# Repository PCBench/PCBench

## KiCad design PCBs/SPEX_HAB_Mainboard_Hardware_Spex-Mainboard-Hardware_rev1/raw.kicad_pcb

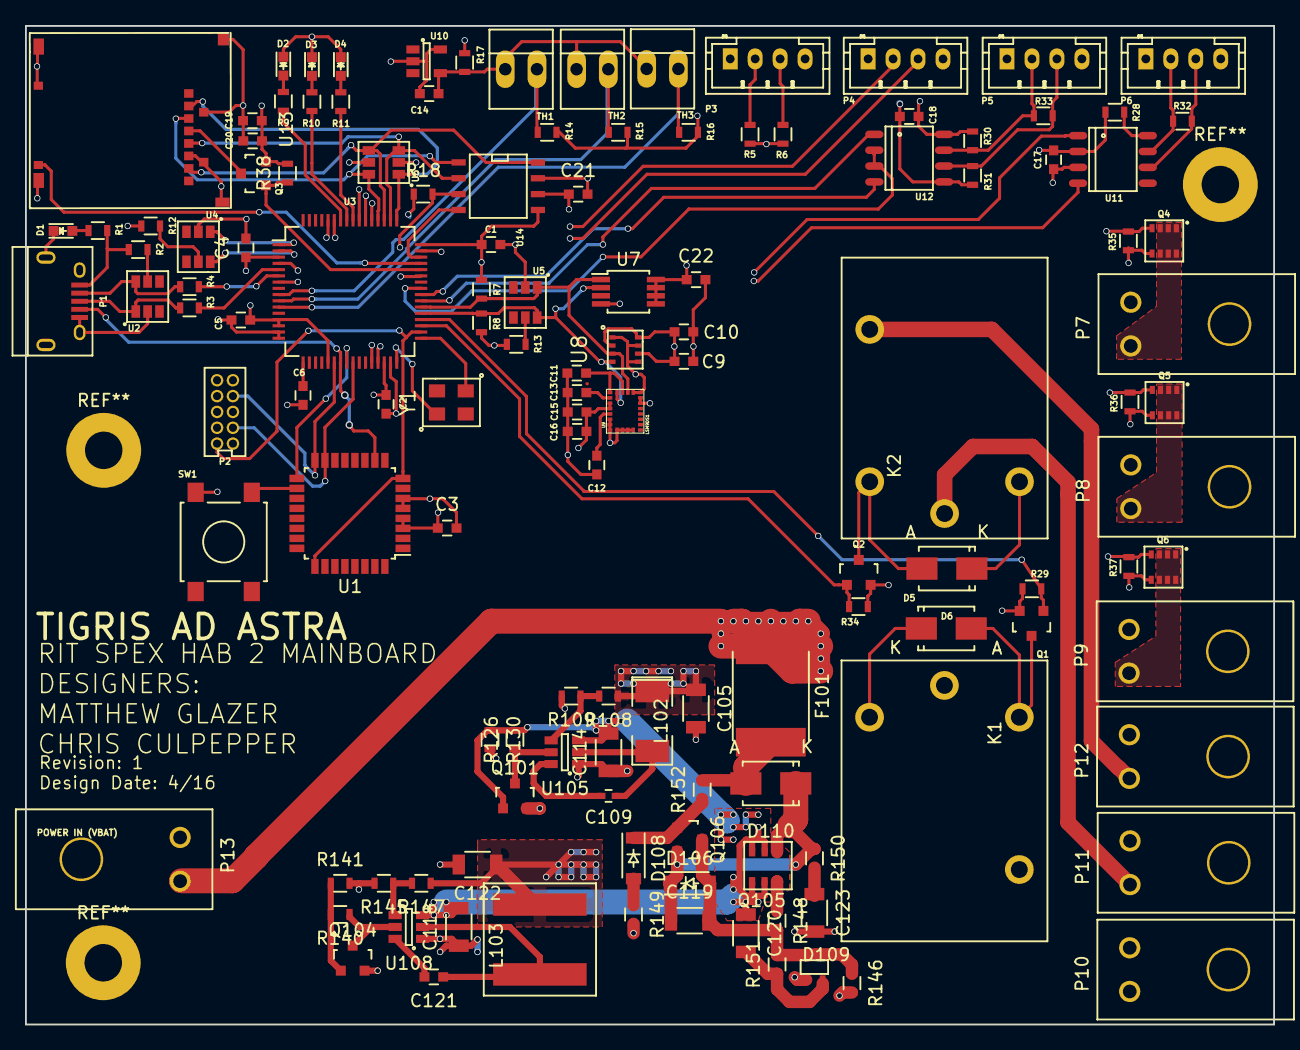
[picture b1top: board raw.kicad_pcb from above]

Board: 4 copper layers, 100.0 x 80.0 mm, 131 parts (0 on the bottom side), 89 nets.

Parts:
C1, C2, C3, C4: 1uF; C_0603
C5: 2.2uF; C_0603
C6, C19: .1uF; C_0603
C9, C10, C17, C18, C21, C22: C; C_0603
C11, C13, C15: 100nF; C_0603
C12: 10nF; C_0603
C14: 4.7uF; C_0603
C16, C20: 10uF; C_0603
C105, C122: 47uf; C_1206
C109: 100nf; C_0402
C114, C118: 22uf; C_1206
C119, C123: 1uf 100v; C_1206
C120: .1uf 100v; C_1206
C121: 100nf; C_0603
D1, D2, D3, D4: LED; LED_0603
D5, D6: FM5819-W; SMA_Standard
D106, D108: ZENER; SOD-123
D109: D_Schottky_x2_Serial_AKC; sc70
D110: DIODE; Diode-SMA_Standard
F101: FUSE; Fuse_SMD2920
K1, K2: G5LE_1A4_DC3; G5LE-1A4-DC3
L102: 2.2uh; SMD-2010_Pol
L103: 3.3uh; NRS8030T3R3MJGJ
P1: USB_OTG; USB_Micro-B
P2: SWD Header; SWD-10
P3, P4, P5, P6: CONN_01X04; JST_PH_B4B-PH-K_04x2.00mm_Straight
P7, P8, P9, P10, P11, P12, P13: CONN_01X02; ultraFitCONN_2
Q1, Q2: 2N7002K; SOT-23
Q3: BSS215PH6327; SOT-23
Q4, Q5, Q6: Si5468DC; ChipFet-8
Q101, Q104: MOS_N_numbered; SOT-23
Q105: Si3407DV
Q106: Q_PNP_BEC; SOT-23
R1, R9, R10, R11: 1K; R_0603
R2, R12, R18, R29, R34, R38, R126, R130, R140, R141: 10K; R_0603
R3, R4: 33; R_0603
R5, R6, R7, R8: 4.7K; R_0603
R13, R30, R31, R35, R36, R37, R109, R145: 10k; R_0603
R14, R15, R16: 12k; R_0603
R17, R28: R; R_0603
R32, R33: 120; R_0603
R108, R146: 33.2k; R_0603
R147: 56.2k; R_0603
R148, R150: 10; R_0603
R149: 27.4k; R_0603
R151: 10.2k; R_0603
R152: 100k; R_0603
SW1: SW_PUSH; SW_SPST_B3S-1000
TH1, TH2, TH3: THERMISTOR; PINHEAD1-2
U1: MKL04Z32VLC4; LQFP-32_7x7mm_Pitch0.8mm
U2, U4, U5: NUP2201MR6; TSOP-6
U3: MK20DX256VLH7; LQFP-64_10x10mm_Pitch0.5mm
U6: MMQA6V2T1G; TSOP-6
U7: MCP9808T; MSOP-8_3x3mm_Pitch0.65mm
U8: BME280; LGA-8
U9: LSM9DS1; LGA-24
U10: LM4030; SOT-23-5
U11: MCP2551-I/SN; SO-8
U12: ST1480ABDR; SO-8
U13: SCHA4B0419; SCH4B0419
U14: AT45DB641E; SOIC-8-N
U105, U108: TPS563200; SOT-23-6
Y1: Crystal; CX3225GB16000D0HPQCC

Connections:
3.3V_MOS_CTRL: Q4.4, R35.2, U3.55
5V_MOS_CTRL: Q5.4, R36.2, U3.54
+3V3: C1.1, C2.1, C3.1, C4.1, C5.1, C9.1, C10.1, C11.1, C15.1, C16.1, C17.1, C18.1, C19.1, C20.1, C21.1, C22.1, C105.1, D5.1, D6.1, K1.4, K2.4, L102.1, P2.1, P3.1, P4.1, P5.1, P6.1, P7.2, Q3.2, R5.2, R6.2, R7.2, R8.2, R12.1, R13.1, R17.1, R18.1, R30.1, R38.2, R108.1, U1.3, U1.4, U3.3, U3.7, U3.13, U3.14, U3.21, U3.30, U3.48, U7.5, U7.6, U7.7, U7.8, U8.2, U8.6, U8.8, U9.1, U9.3, U9.7, U9.8, U9.22, U9.23, U11.3, U12.8, U14.5, U14.6
+5V: C122.1, L103.1, P8.2, R147.1
/Data_Input_Output/3.3V_MOS_OUT: P7.1, Q4.1, Q4.2, Q4.3, Q4.6, Q4.7, Q4.8
/Data_Input_Output/5V_MOS_OUT: P8.1, Q5.1, Q5.2, Q5.3, Q5.6, Q5.7, Q5.8
/Data_Input_Output/Battery_Out: K1.3, P10.1
/Data_Input_Output/CANH_out: P6.2, R32.1, U11.7
/Data_Input_Output/CANL_out: P6.3, R32.2, U11.6
/Data_Input_Output/RS485_A: P5.3, R31.1, R33.2, U12.6
/Data_Input_Output/RS485_B: P5.2, R30.2, R33.1, U12.7
/Data_Input_Output/User_In: K2.1, P11.1
/Data_Input_Output/User_Out: K2.3, P12.1
/Data_Input_Output/Vbus_MOS_OUT: P9.1, Q6.1, Q6.2, Q6.3, Q6.6, Q6.7, Q6.8
/HAB Sensors/2.5VRefVoltage: C14.1, R17.2, TH1.1, TH2.1, TH3.1, U10.4
/PTA6: P1.4, U1.10, U3.23
/PTA7: P2.2, U1.15, U3.25
/PTB0: P2.4, U1.16, U3.22
/PTB1: U1.17, U3.24
/PTB2: SW1.1, U1.18
CAN0_RX: U3.29, U11.4
CAN0_TX: U3.28, U11.1
Flash_Reset: R18.2, U3.43, U14.3
GND: C1.2, C2.2, C3.2, C4.2, C5.2, C6.2, C9.2, C10.2, C11.2, C12.2, C13.2, C14.2, C15.2, C16.2, C17.2, C18.2, C19.2, C20.2, C21.2, C22.2, C105.2, C114.1, C118.1, C122.2, C123.2, D1.1, D2.1, D3.1, D4.1, D109.1, P1.5, P1.6, P2.3, P2.5, P3.4, P4.4, P5.4, P6.4, P10.2, P11.2, P12.2, P13.1, Q1.2, Q2.2, Q4.5, Q5.5, Q6.5, Q101.2, Q104.2, R14.2, R15.2, R16.2, R28.2, R29.2, R31.2, R34.2, R35.1, R36.1, R37.1, R109.2, R130.2, R141.2, R145.2, R146.2, R149.2, SW1.2, U1.5, U1.6, U2.2, U3.4, U3.15, U3.16, U3.31, U3.47, U4.2, U5.2, U6.2, U6.5, U7.4, U8.1, U8.5, U8.7, U9.5, U9.6, U9.14, U9.15, U9.16, U9.17, U9.18, U9.19, U9.20, U10.2, U10.5, U11.2, U12.5, U13.6, U13.10, U14.7, U105.1, U108.1
I2C0_SCL: R8.1, U3.37, U5.6, U7.2, U8.4, U9.2
I2C0_SDA: R7.1, U3.38, U5.1, U7.1, U8.3, U9.4
I2C1_SCL: P3.3, R6.1, U3.2, U4.6
I2C1_SDA: P3.2, R5.1, U3.1, U4.1
LED_Heartbeat: R9.1, U3.58
LED_Status_1: R10.1, U3.57
LED_Status_2: R11.1, U3.56
unnamed: C6.1, U3.17
unnamed: C12.1, U9.21
unnamed: C13.1, U9.24
unnamed: C109.1, L102.2, U105.2
unnamed: C109.2, U105.6
unnamed: C119.1, D106.1, D110.1, Q105.4, Q106.2, R150.1
unnamed: C119.2, D106.2, D109.3, Q106.3, R146.1, R148.2, R151.2
unnamed: C120.2, D109.2, R151.1
unnamed: C121.1, L103.2, U108.2
unnamed: C121.2, U108.6
unnamed: C123.1, R150.2
unnamed: D1.2, R1.2
unnamed: D2.2, R9.2
unnamed: D3.2, R10.2
unnamed: D4.2, R11.2
unnamed: D5.2, K1.2, Q1.3
unnamed: D6.2, K2.2, Q2.3
unnamed: D108.1, Q106.1, R152.1
unnamed: D108.2, R149.1
unnamed: D110.2, F101.2, R152.2
unnamed: P1.1, R1.1, R2.2
unnamed: P1.2, R4.2, U2.6
unnamed: P1.3, R3.2, U2.1
unnamed: Q3.3, U13.4
unnamed: Q101.3, R126.1, U105.5
unnamed: Q104.3, R140.1, U108.5
unnamed: Q105.3, R148.1
unnamed: R2.1, U2.5
unnamed: R3.1, U3.5
unnamed: R4.1, U3.6
unnamed: R12.2, U4.5
unnamed: R13.2, U5.5
unnamed: R28.1, U11.8
unnamed: R108.2, R109.1, U105.4
unnamed: R145.1, R147.2, U108.4
unnamed: U3.32, Y1.1
unnamed: U3.33, Y1.2
RESET_b: P2.10, U1.8, U1.25, U3.34
RX/TX_CTRL: U3.41, U12.2, U12.3
Relay1_ctrl: Q1.1, R29.1, U3.36
Relay2_ctrl: Q2.1, R34.1, U3.35
SD_CTRL: Q3.1, R38.1, U3.44
SD_Detect: U3.45, U13.9
SPI0_CS0: U3.49, U6.1, U13.2
SPI0_CS1: U3.46, U14.4
SPI0_MISO: U3.51, U6.4, U13.7, U14.8
SPI0_MOSI: U3.52, U6.6, U13.3, U14.1
SPI0_SCK: U3.50, U6.3, U13.5, U14.2
Temp1: R14.1, TH1.2, U3.9
Temp2: R15.1, TH2.2, U3.10
Temp3: R16.1, TH3.2, U3.11
UART0_RX: U3.39, U12.1
UART0_TX: U3.40, U12.4
UART2_RX: P4.3, U3.59
UART2_TX: P4.2, U3.60
VBatt: F101.1, K1.1, P13.2
Vbus: C114.2, C118.2, C120.1, P9.2, Q101.1, Q104.1, Q105.1, Q105.2, Q105.5, Q105.6, R126.2, R130.1, R140.2, R141.1, U105.3, U108.3
Vbus_MOS_CTRL: Q6.4, R37.2, U3.53

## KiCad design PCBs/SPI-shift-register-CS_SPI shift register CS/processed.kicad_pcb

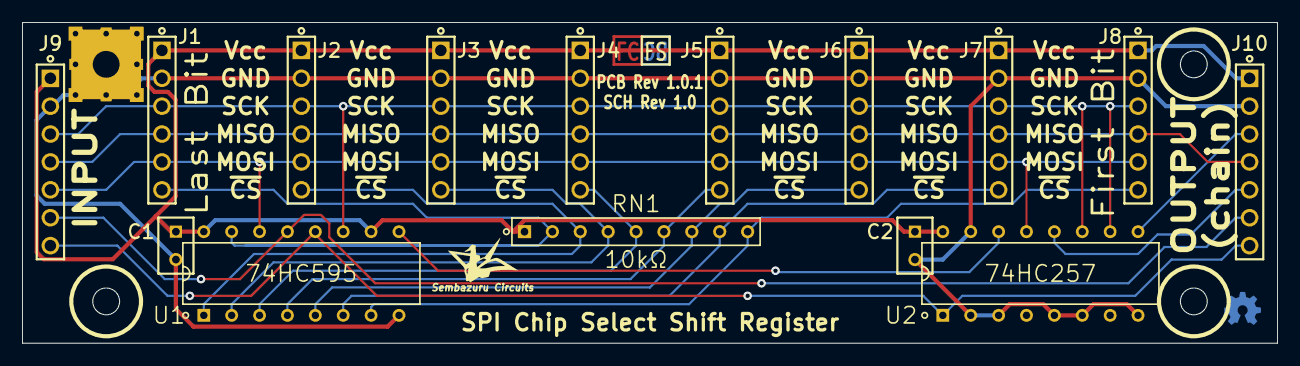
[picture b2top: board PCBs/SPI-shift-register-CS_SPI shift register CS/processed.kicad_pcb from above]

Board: 2 copper layers, 114.3 x 29.2 mm, 20 parts (0 on the bottom side), 18 nets.

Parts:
C1, C2: 0.1µF; CAPRR254W51L508T318H660P
J1, J2, J3, J4, J5, J6, J7, J8: CONN_06; HDRV6W64P254_1X6_1524X254X1016P
J9, J10: CONN_07; HDRV7W64P254_1X7_1778X254X1016P
LayerIcon02: VAL**; LayerIcon02
MH1: #2 Free Fit; MTGP635H244V8P
MH2, MH3, MH4: #2 Free Fit; MTGNP635H244Z635P
RN1: 10kΩ; SIP249W55P254L2261H495Q9C
U1: 74HC595; DIP762W52P254L2159H381Q16C
U2: 74HC257; DIP762W52P254L2159H381Q16C

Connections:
/MISO: J1.4, J2.4, J3.4, J4.4, J5.4, J6.4, J7.4, J8.4, J9.4, J10.4
/MOSI: J1.5, J2.5, J3.5, J4.5, J5.5, J6.5, J7.5, J8.5, J9.5, U1.14, U2.13
/MOSI/Ser: J10.5, U2.12
/SCK: J1.3, J2.3, J3.3, J4.3, J5.3, J6.3, J7.3, J8.3, J9.3, U1.11, U2.10, U2.11
/SCKdelayed: J10.3, U2.9
/SerChain: U1.9, U2.14
/~CS1: J1.6, RN1.2, U1.15
/~CS2: J2.6, RN1.3, U1.1
/~CS3: J3.6, RN1.4, U1.2
/~CS4: J4.6, RN1.5, U1.3
/~CS5: J5.6, RN1.6, U1.4
/~CS6: J6.6, RN1.7, U1.5
/~CS7: J7.6, RN1.8, U1.6
/~CS8: J8.6, RN1.9, U1.7
/~dCS: J9.6, J10.6, U1.13
/~rCS: J9.7, J10.7, U1.12, U2.1
GND: C1.2, C2.2, J1.2, J2.2, J3.2, J4.2, J5.2, J6.2, J7.2, J8.2, J9.2, J10.2, MH1.0, U1.8, U2.2, U2.3, U2.5, U2.6, U2.8, U2.15
VCC: C1.1, C2.1, J1.1, J2.1, J3.1, J4.1, J5.1, J6.1, J7.1, J8.1, J9.1, J10.1, RN1.1, U1.10, U1.16, U2.16

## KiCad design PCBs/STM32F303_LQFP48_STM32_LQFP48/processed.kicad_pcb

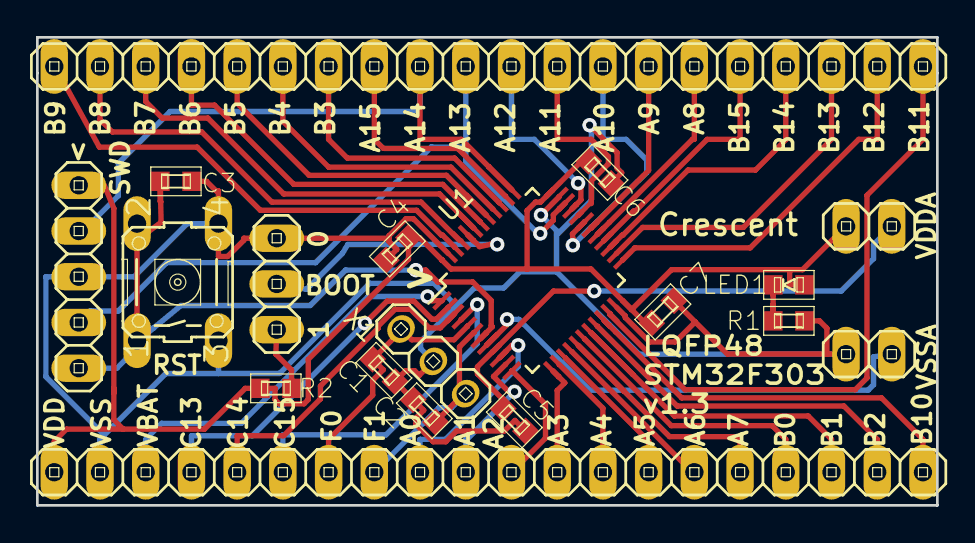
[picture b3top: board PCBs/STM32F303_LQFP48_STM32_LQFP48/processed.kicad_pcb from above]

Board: 2 copper layers, 50.0 x 26.0 mm, 19 parts (0 on the bottom side), 46 nets.

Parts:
C1, C2, C3, C4, C5, C6, C7: CAPACITOR1608; generic-SMD1608
JP1: PINHD-1X5; pinhead-1X05
JP2: PINHD-1X3; pinhead-1X03
JP3, JP5: PINHD-1X2; pinhead-1X02
JP4, JP6: PINHD-1X20; pinhead-1X20
LED1: LED1608; generic-LED1608
R1, R2: RESISTOR1608; generic-SMD1608
S1: 10-XX; switch-omron-B3F-10XX
U1: STM32F100C8; LQFP-48_7x7mm_Pitch0.5mm
X1: CRYSTAL_SMD; pinhead-1X03

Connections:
BOOT: JP2.2, U1.44
NRST: C3.1, JP1.5, S1.1, S1.2, U1.7
unnamed: JP2.1, R2.2
unnamed: LED1.K, R1.1
OSCI: C1.1, JP4.7, U1.5, X1.1
OSCO: C2.1, JP4.8, U1.6, X1.2
PA0: JP4.9, U1.10
PA1: JP4.10, U1.11
PA2: JP4.11, U1.12
PA3: JP4.12, U1.13
PA4: JP4.13, U1.14
PA5: JP4.14, U1.15
PA6: JP4.15, U1.16
PA7: JP4.16, U1.17
PA8: JP6.15, U1.29
PA9: JP6.14, U1.30
PA10: JP6.13, U1.31
PA11: JP6.12, U1.32
PA12: JP6.11, U1.33
PA13: JP1.4, JP6.10, U1.34
PA14: JP1.2, JP6.9, U1.37
PA15: JP6.8, U1.38
PB0: JP4.17, U1.18
PB1: JP4.18, U1.19
PB2: JP4.19, U1.20
PB3: JP6.7, U1.39
PB4: JP6.6, U1.40
PB5: JP6.5, U1.41
PB6: JP6.4, U1.42
PB7: JP6.3, U1.43
PB8: JP6.2, U1.45
PB9: JP6.1, U1.46
PB10: JP4.20, U1.21
PB11: JP6.20, U1.22
PB12: JP6.19, U1.25
PB13: JP6.18, U1.26
PB14: JP6.17, U1.27
PB15: JP6.16, U1.28
PC13: JP4.4, U1.2
PC14: JP4.5, U1.3
PC15: JP4.6, U1.4
VBAT: JP4.3, U1.1
VDD: C4.1, C6.1, C7.1, JP1.1, JP3.1, JP4.1, LED1.A, R2.1, U1.24, U1.36, U1.48
VDDA: C5.1, JP3.2, U1.9
VSS: C1.2, C2.2, C3.2, C4.2, C5.2, C6.2, C7.2, JP1.3, JP2.3, JP4.2, JP5.1, R1.2, S1.3, S1.4, U1.23, U1.35, U1.47, X1.3
VSSA: JP5.2, U1.8

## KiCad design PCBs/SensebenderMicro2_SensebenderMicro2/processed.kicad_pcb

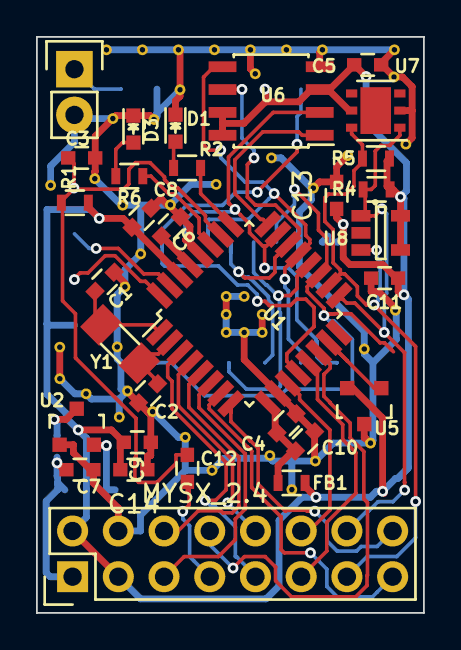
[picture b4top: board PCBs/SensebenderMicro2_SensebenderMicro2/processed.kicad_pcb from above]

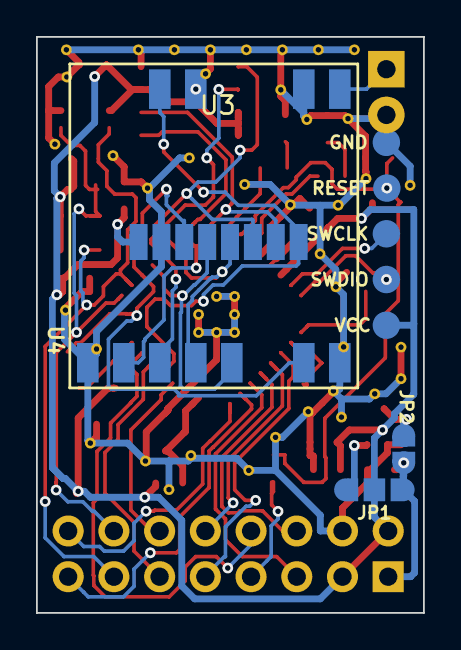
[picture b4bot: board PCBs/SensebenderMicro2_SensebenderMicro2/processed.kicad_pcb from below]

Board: 2 copper layers, 21.5 x 32.0 mm, 40 parts (9 on the bottom side), 37 nets.

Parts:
C1, C2, C4, C5, C6, C7, C8, C9, C13: 100nF; C_0603
C3: 10nF; C_0603
C10, C11, C14: 10uF; C_0603
C12: C; C_0603
D1, D3: LED; LED-0603
FB1: FILTER; R_0603
JP1: PWR SELECT; 3_pin_solder_jumper_smd
JP2: JUMPER; 2_pin_solder_jumper_smd
P2: MYSX_2.4
P3: Antenna; Pin_Header_Straight_1x02
R1: 100K; R_0603
R2, R6: 220R; R_0603
R4, R5: 4k7; R_0603
U1: ATSAMD20E; TQFP-32_7x7mm_Pitch0.8mm
U2: MCP1703T-3302E; SOT-23
U3: NRF24L01; NRF24L01-SMD
U4: RFM69HW; RFM95HW_SMD
U5: ATSHA204A; SOT-23
U6: AT45DB041E; SOIC-8_3.9x4.9mm_Pitch1.27mm
U7: Si7021; DFN-6-1EP_3x3mm_Pitch0.95mm
U8: 24AA32AT-I/OT; SOT-23-5
W1: GND; Measurement_Point_Round-SMD-Pad_Small
W2: RESET; Measurement_Point_Round-SMD-Pad_Small
W3: SWCLK; Measurement_Point_Round-SMD-Pad_Small
W4: SWDIO; Measurement_Point_Round-SMD-Pad_Small
W5: VCC; Measurement_Point_Round-SMD-Pad_Small
Y1: 32Khz; XTAL_3.2x1.5mm

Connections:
+3.3VA: C4.2, C10.1, FB1.2, U1.9
+3V3: C5.2, C8.1, C9.2, C11.1, C13.1, C14.2, FB1.1, JP1.2, P2.2, P2.3, R1.1, R4.1, R5.1, U1.30, U3.2, U4.13, U5.2, U6.3, U6.7, U6.8, U7.5, U8.4, U8.5, W5.1
/ANT: P3.1, U4.9
/CSN: U1.20, U3.4, U4.5
/D1_DFM: P2.5, U1.6
/D2_DTM: P2.6, U1.5
/D3_INT: P2.9, U1.3
/D4_INT: P2.10, U1.4
/D5_PWM: P2.11, U1.13
/D6_PWM: P2.12, U1.11
/D7_SCL: P2.13, R5.2, U1.18, U7.6, U8.3
/D8_SDA: P2.14, R4.2, U1.17, U7.1, U8.1
/D9_A3: P2.15, U1.7
/D10_A4: P2.16, U1.8
/FLS_CS: U1.24, U6.1
/IRQ: U1.12, U3.8, U4.14
/LEGACY_ID: P2.8, U1.14
/MISO: U1.23, U3.7, U4.2, U6.2
/MOSI: U1.21, U3.6, U4.3, U6.5
/NRF_CE_RFM_DIO5: U1.19, U3.3, U4.7
/RESET: C3.1, C12.1, R1.2, U1.26, W2.1
/RST: C12.2, P2.7
/SCK: U1.22, U3.5, U4.4, U6.6
/SECURITY: U1.15, U5.1
/SWCLK: U1.31, W3.1
/SWDIO: U1.32, W4.1
/V_RAW: C7.1, JP1.3, JP2.1, P2.1
GND: C1.1, C2.1, C3.2, C4.1, C5.1, C6.1, C7.2, C8.2, C9.1, C10.2, C11.2, C13.2, C14.1, D1.1, D3.1, P2.4, P3.2, U1.10, U1.28, U2.1, U3.1, U4.1, U4.8, U4.10, U5.3, U6.4, U7.2, W1.1
unnamed: C1.2, U1.1, Y1.1
unnamed: C2.2, U1.2, Y1.2
unnamed: C6.2, U1.29
unnamed: D1.2, R2.2
unnamed: D3.2, R6.2
unnamed: JP1.1, U2.2
unnamed: JP2.2, U2.3
unnamed: R2.1, U1.25
unnamed: R6.1, U1.27

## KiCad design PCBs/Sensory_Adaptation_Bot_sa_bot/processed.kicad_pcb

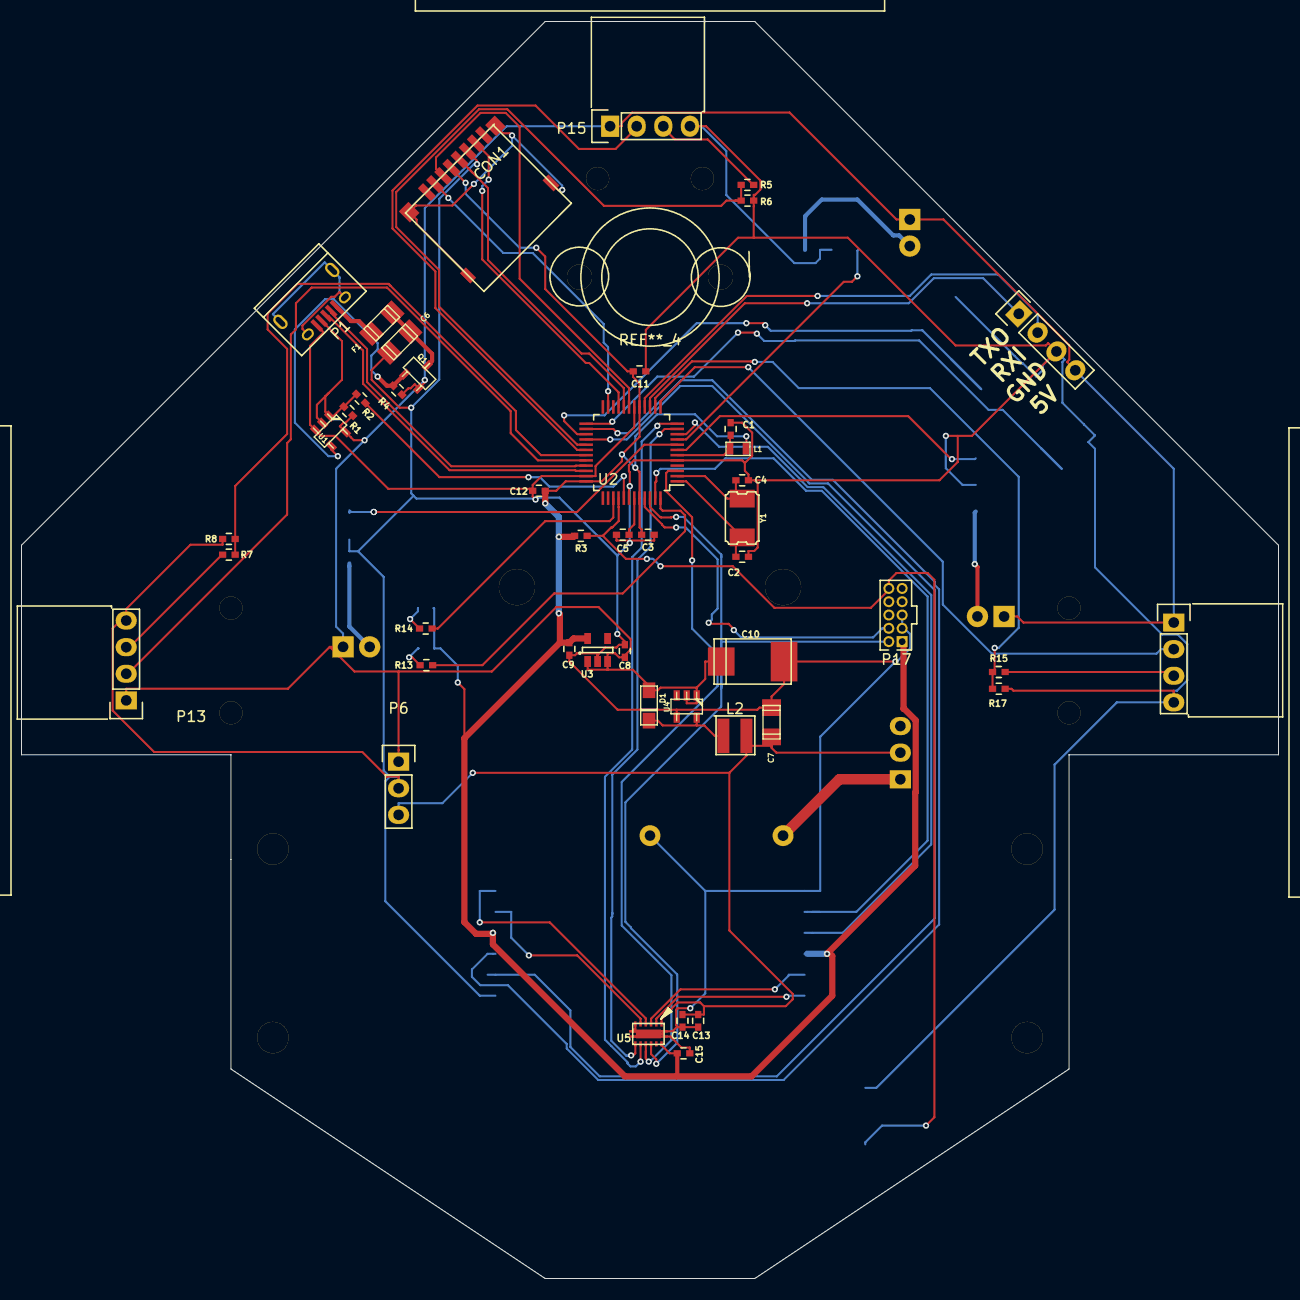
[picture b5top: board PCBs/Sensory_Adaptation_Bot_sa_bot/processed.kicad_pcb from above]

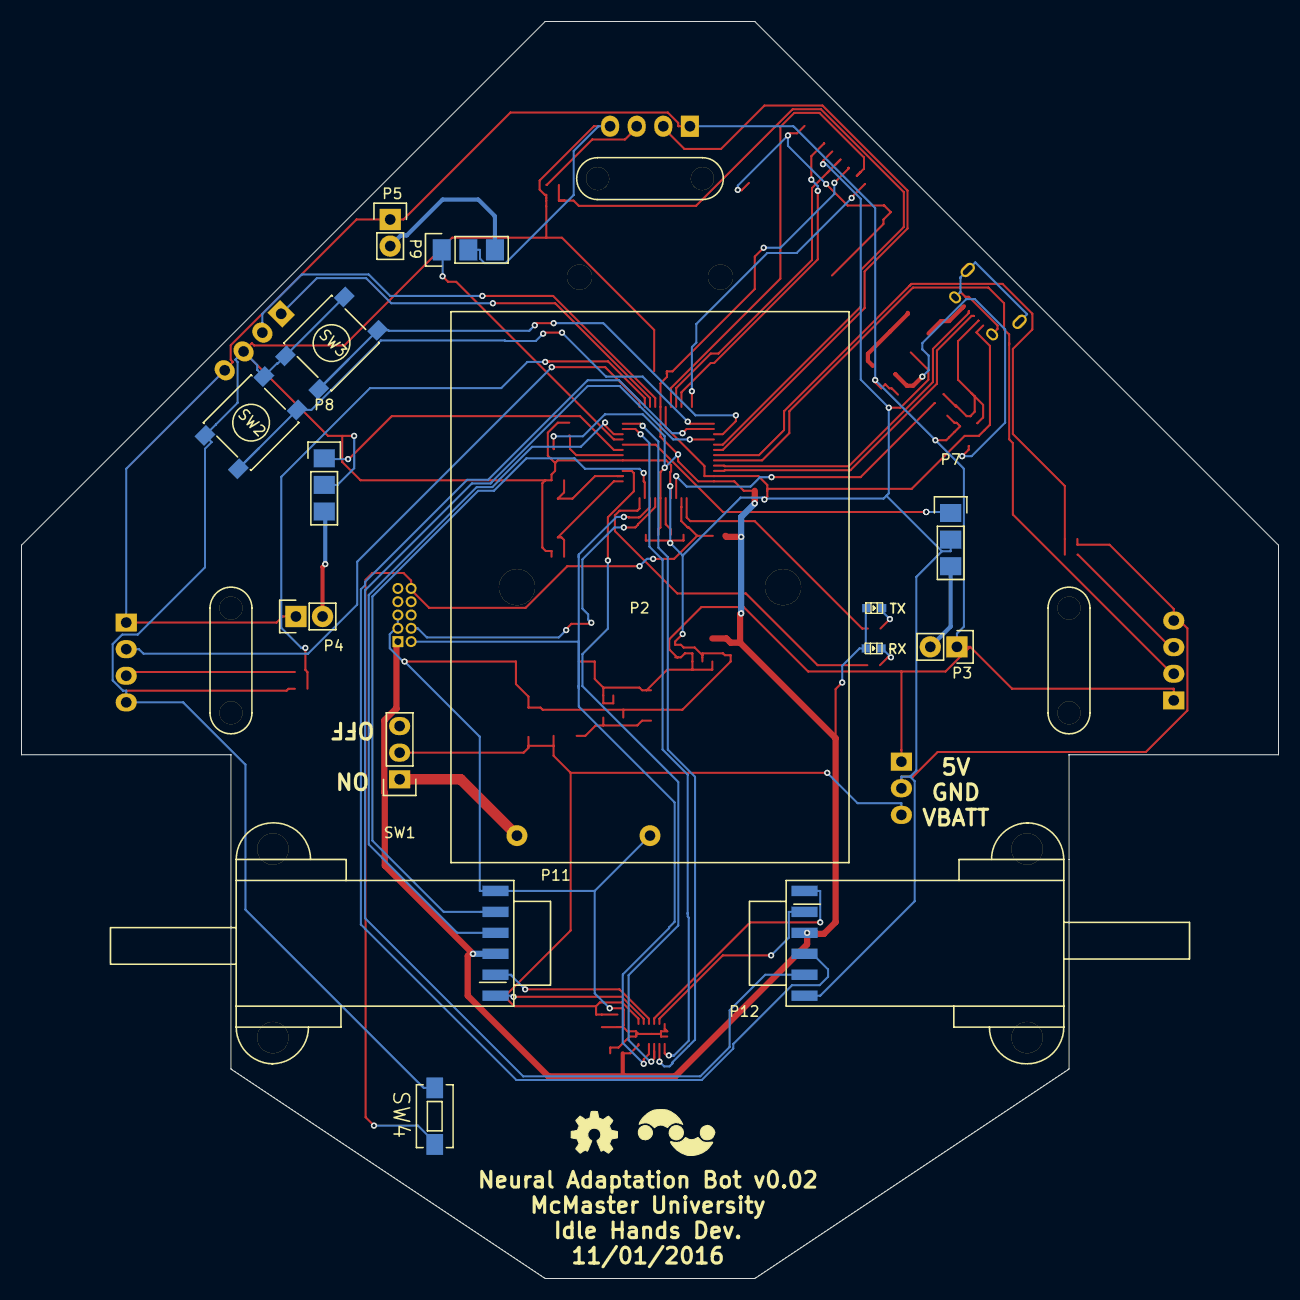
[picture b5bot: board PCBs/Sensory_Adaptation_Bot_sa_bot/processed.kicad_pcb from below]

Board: 2 copper layers, 120.0 x 120.0 mm, 61 parts (15 on the bottom side), 58 nets.

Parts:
C1, C3, C5, C11, C12, C14, C15: 0.1uF; C_0402_Hand
C2, C4: 15pF; C_0402_Hand
C6: 2.2uF; c_1206
C7: 10uF; c_1206
C8: 1uF; C_0402_Hand
C9: 2.2uF; C_0402_Hand
C10: 68uF; TantalC_SizeV_EIA-7343
C13: 10uF; C_0402_Hand
CON1: MicroSD_Card; MicroSD_Card_Receptacle
D1: BAT20J; sod323
D6: RX; Led_0603
D7: TX; Led_0603
F1: 500mA; c_1206
L1: FB - 30Ohm; R_SM0603
L2: 47uH; I_1212
P1: USB_OTG; USB_Micro-B
P2: BatteryHolder; Battery_3xAAA_Holder
P3: IR4_JMP; Pin_Header_Straight_1x02
P4: IR2_JMP; Pin_Header_Straight_1x02
P5: IR3_JMP; Pin_Header_Straight_1x02
P6: ExPower; Pin_Header_Straight_1x03
P7: IR_4; Pin_Header_SMD_1x03
P8: IR_2; Pin_Header_SMD_1x03
P9: IR_3; Pin_Header_SMD_1x03
P11: MOTOR_A; Motor_Pololu_Encoder
P12: MOTOR_B; Motor_Pololu_Encoder
P13: SONAR_4; SonarSensor_HCSR04
P14: SONAR_2; SonarSensor_HCSR04
P15: SONAR_3; SonarSensor_HCSR04
P17: DBG_CONN; Pin_Header_Straight_2x05_Pitch1.27mm
P18: CONN_01X04; Pin_Header_Straight_1x04
Q1: Q_PMOS_DSG; SOT23_DSG
R1: 100k; R_0402_Hand
R2: 330; R_0402_Hand
R3, R5, R6, R7, R8, R15, R17: 10k; R_0402_Hand
R4: 47K; R_0402_Hand
R13, R14: 1k; R_0402_Hand
SW1: SWITCH_INV; Pin_Header_Straight_1x03
SW2, SW3: SW_PUSH; SW_SPST_PTS645
SW4: SW_PUSH; SW_SPST_EVQPE1
U1: 74AHC1G125; sot23-5
U2: SAMD21G18; TQFP-48_7x7mm_Pitch0.5mm
U3: AP2112K-3.3V; SOT-23-5
U4: NCP1402; sot23-5
U5: DRV8835; WSON-12-2x3
Y1: Crystal_Small; crystal_smd_5x3.2mm

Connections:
+3V3: C3.1, C9.1, C11.1, C12.1, C15.1, CON1.4, D6.2, D7.2, L1.1, P11.3, P12.3, P17.1, R3.1, U2.17, U2.36, U2.44, U3.5, U5.12
/AENC1: P11.4, U2.10
/AENC2: P11.5, U2.47
/AIN2: U2.3, U5.9
/AM1: P11.1, U5.2
/AM2: P11.2, U5.3
/BENC1: P12.4, U2.26
/BENC2: P12.5, U2.28
/BIN1: U2.12, U5.8
/BIN2: U2.11, U5.7
/BM1: P12.1, U5.4
/BM2: P12.2, U5.5
/BUT1: SW2.1, U2.25
/BUT2: SW3.1, U2.27
/ECHO2: R15.1, R17.2, U2.14
/ECHO3: R5.1, R6.2, U2.29
/ECHO4: R7.1, R8.2, U2.31
/HVECHO2: P14.2, R15.2
/HVECHO3: P15.2, R5.2
/HVECHO4: P13.2, R7.2
/IR2: P8.1, U2.7
/IR3: P9.1, U2.9
/IR4: P7.1, U2.8
/RXI: P18.2, U2.16
/RXLED: R13.1, U2.48
/SD_CS: CON1.2, U2.23
/SPI_MISO: CON1.7, U2.21
/SPI_MOSI: CON1.3, U2.19
/SPI_SCK: CON1.5, U2.20
/TRIG2: P14.3, U2.13
/TRIG3: P15.3, U2.30
/TRIG4: P13.3, U2.32
/TXLED: R14.1, U2.39
/TXO: P18.1, U2.15
GND: C1.2, C2.2, C3.2, C4.2, C5.2, C6.2, C7.2, C8.2, C9.2, C10.2, C11.2, C12.2, C13.2, C14.2, C15.2, CON1.6, P1.5, P2.1, P6.2, P7.2, P8.2, P9.2, P11.6, P12.6, P13.1, P14.1, P15.1, P17.3, P17.5, P18.3, R6.1, R8.1, R17.1, SW2.2, SW3.2, SW4.2, U1.3, U2.5, U2.18, U2.35, U2.42, U3.2, U4.4, U5.6
unnamed: C1.1, L1.2, U2.6
unnamed: C2.1, U2.1, Y1.2
unnamed: C4.1, U2.2, Y1.1
unnamed: C5.1, U2.43
unnamed: D1.2, L2.2, U4.5
unnamed: D6.1, R13.2
unnamed: D7.1, R14.2
unnamed: F1.1, P1.1
unnamed: P3.2, P7.3
unnamed: P4.2, P8.3
unnamed: P5.2, P9.3
unnamed: Q1.3, R4.2, U1.4
RESET: P17.10, R3.2, SW4.1, U2.40
SBATT: C7.1, C13.1, C14.1, L2.1, P6.3, SW1.2, U5.1
SWCLK: P17.4, U2.45
SWDIO: P17.2, U2.46, U5.10
USB_D+: P1.3, U2.34
USB_D-: P1.2, U2.33
USB_HOST_EN: R2.2, U2.41
USB_ID: P1.4, R1.2, R2.1, U1.1, U1.2
VBATT: P2.2, SW1.1
VCC: C8.1, C10.1, D1.1, P3.1, P4.1, P5.1, P6.1, P13.4, P14.4, P15.4, P18.4, Q1.2, R1.1, R4.1, U1.5, U3.1, U3.3, U4.1, U4.2
VCOM: C6.1, F1.2, Q1.1
